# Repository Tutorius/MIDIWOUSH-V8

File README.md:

# MIDIWOUSH-V8
USB-MIDI-CV-Interface with 8 outputs

All Files for the USB-MIDI-CV-Interface with 8 Outputs

a.) Software & Hardware
Files for ARDUINO IDE. Used Hardware ESP32-S3-WROOM (AliExpress), TCA9548A, GY-MCP4728, 1,30"" IIC Display (all AliExpress)
4 push-buttons (AliExpress)

b.) PCB
KiCAD-Files

To Do:

c.) PCB-Production
PCBWay-Link to project

e.) 3D-files
Files for frontplate, mounting-things, casing for use out of modular System

More Info about use and problems:

At the time i did not find a way to alter the "Midi-Name" (Its something like "ESP32S3_DEV MIDI 1"). Would be nice if it can be named "MIDIWOUSH-V8". Will try to get a solution for this.

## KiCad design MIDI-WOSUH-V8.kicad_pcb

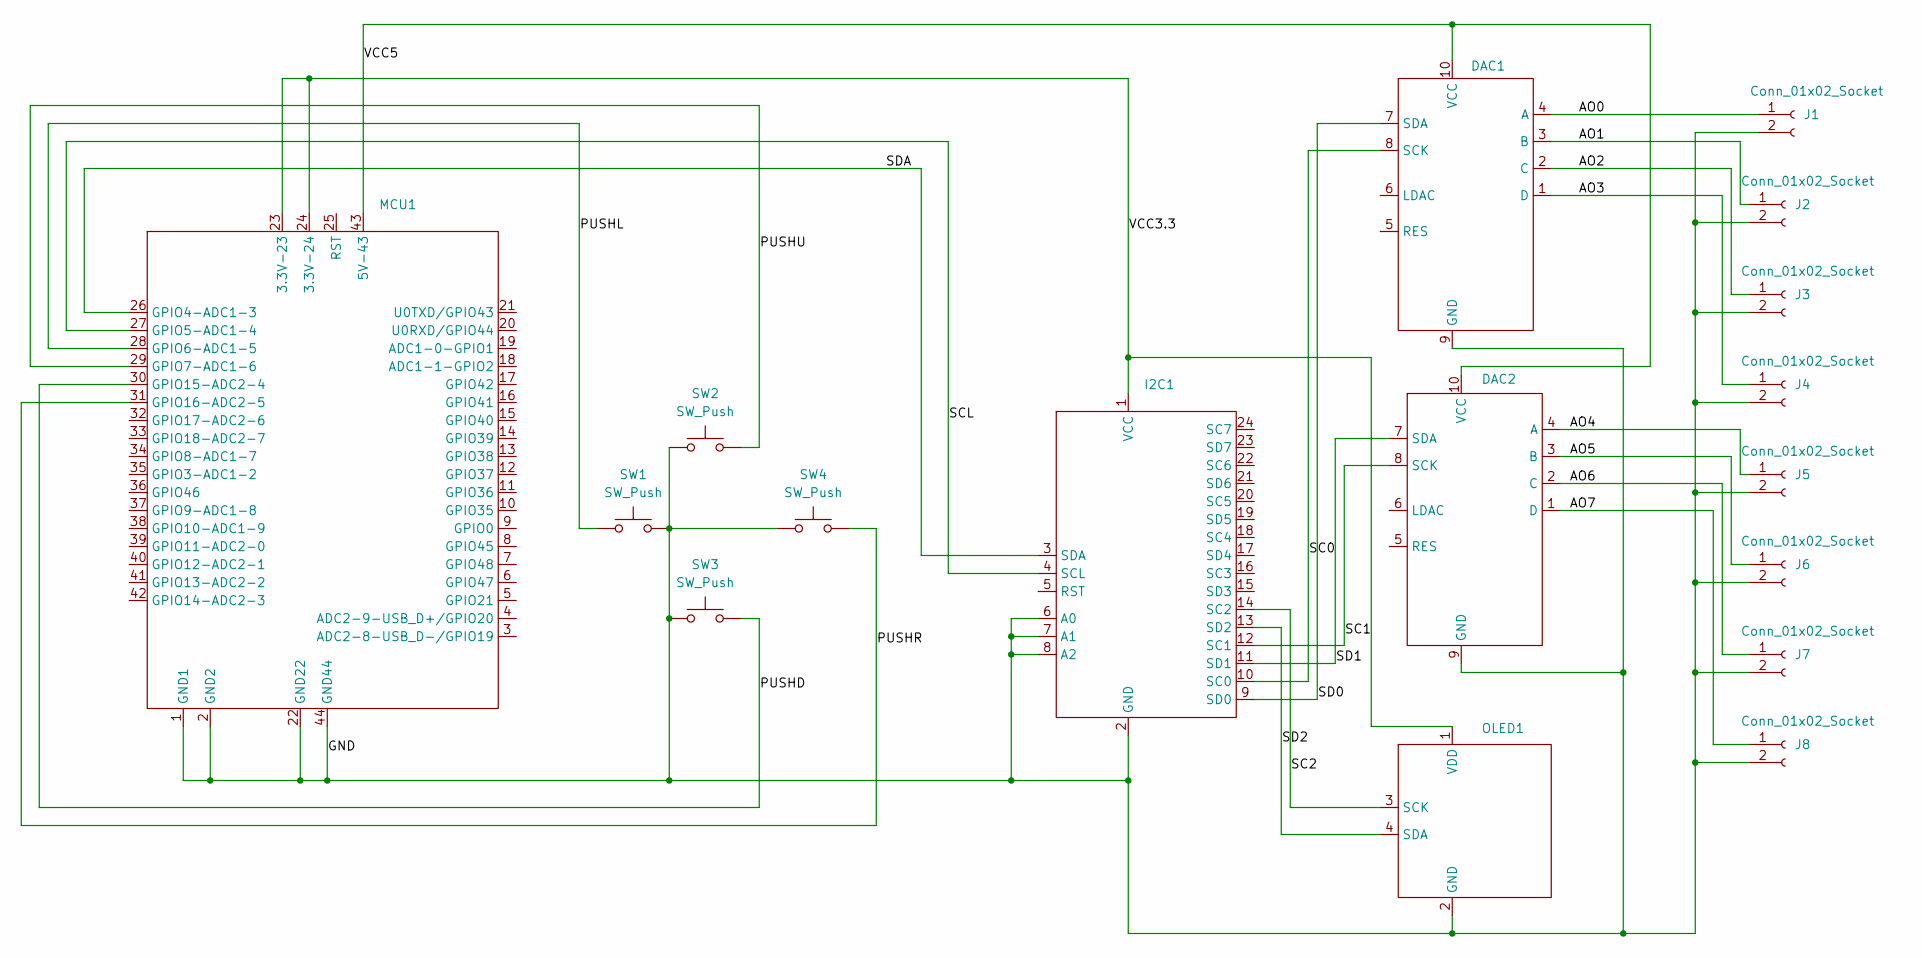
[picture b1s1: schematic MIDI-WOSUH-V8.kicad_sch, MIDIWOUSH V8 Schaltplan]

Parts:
DAC1, DAC2: MCP4728
I2C1: TCA9548A
J1, J2, J3, J4, J5, J6, J7, J8: Conn_01x02_Socket; PinSocket_1x02_P2.54mm_Vertical
MCU1: ESP32-S3-DevKitC-1
OLED1: OLED
SW1, SW2, SW3, SW4: SW_Push; SWITCH1

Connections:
/AO0: DAC1.4 (A), J1.1
/AO1: DAC1.3 (B), J2.1
/AO2: DAC1.2 (C), J3.1
/AO3: DAC1.1 (D), J4.1
/AO4: DAC2.4 (A), J5.1
/AO5: DAC2.3 (B), J6.1
/AO6: DAC2.2 (C), J7.1
/AO7: DAC2.1 (D), J8.1
/GND: DAC1.9 (GND), DAC2.9 (GND), I2C1.2 (GND), I2C1.6 (A0), I2C1.7 (A1), I2C1.8 (A2), J1.2, J2.2, J3.2, J4.2, J5.2, J6.2, J7.2, J8.2, MCU1.1 (GND1), MCU1.2 (GND2), MCU1.22 (GND22), MCU1.44 (GND44), OLED1.2 (GND), SW1.2, SW2.1, SW3.1, SW4.1
/PUSHD: MCU1.30 (GPIO15-ADC2-4), SW3.2
/PUSHL: MCU1.28 (GPIO6-ADC1-5), SW1.1
/PUSHR: MCU1.31 (GPIO16-ADC2-5), SW4.2
/PUSHU: MCU1.29 (GPIO7-ADC1-6), SW2.2
/SC0: DAC1.8 (SCK), I2C1.10 (SC0)
/SC1: DAC2.8 (SCK), I2C1.12 (SC1)
/SC2: I2C1.14 (SC2), OLED1.3 (SCK)
/SCL: I2C1.4 (SCL), MCU1.27 (GPIO5-ADC1-4)
/SD0: DAC1.7 (SDA), I2C1.9 (SD0)
/SD1: DAC2.7 (SDA), I2C1.11 (SD1)
/SD2: I2C1.13 (SD2), OLED1.4 (SDA)
/SDA: I2C1.3 (SDA), MCU1.26 (GPIO4-ADC1-3)
/VCC3.3: I2C1.1 (VCC), MCU1.23 (3.3V-23), MCU1.24 (3.3V-24), OLED1.1 (VDD)
/VCC5: DAC1.10 (VCC), DAC2.10 (VCC), MCU1.43 (5V-43)

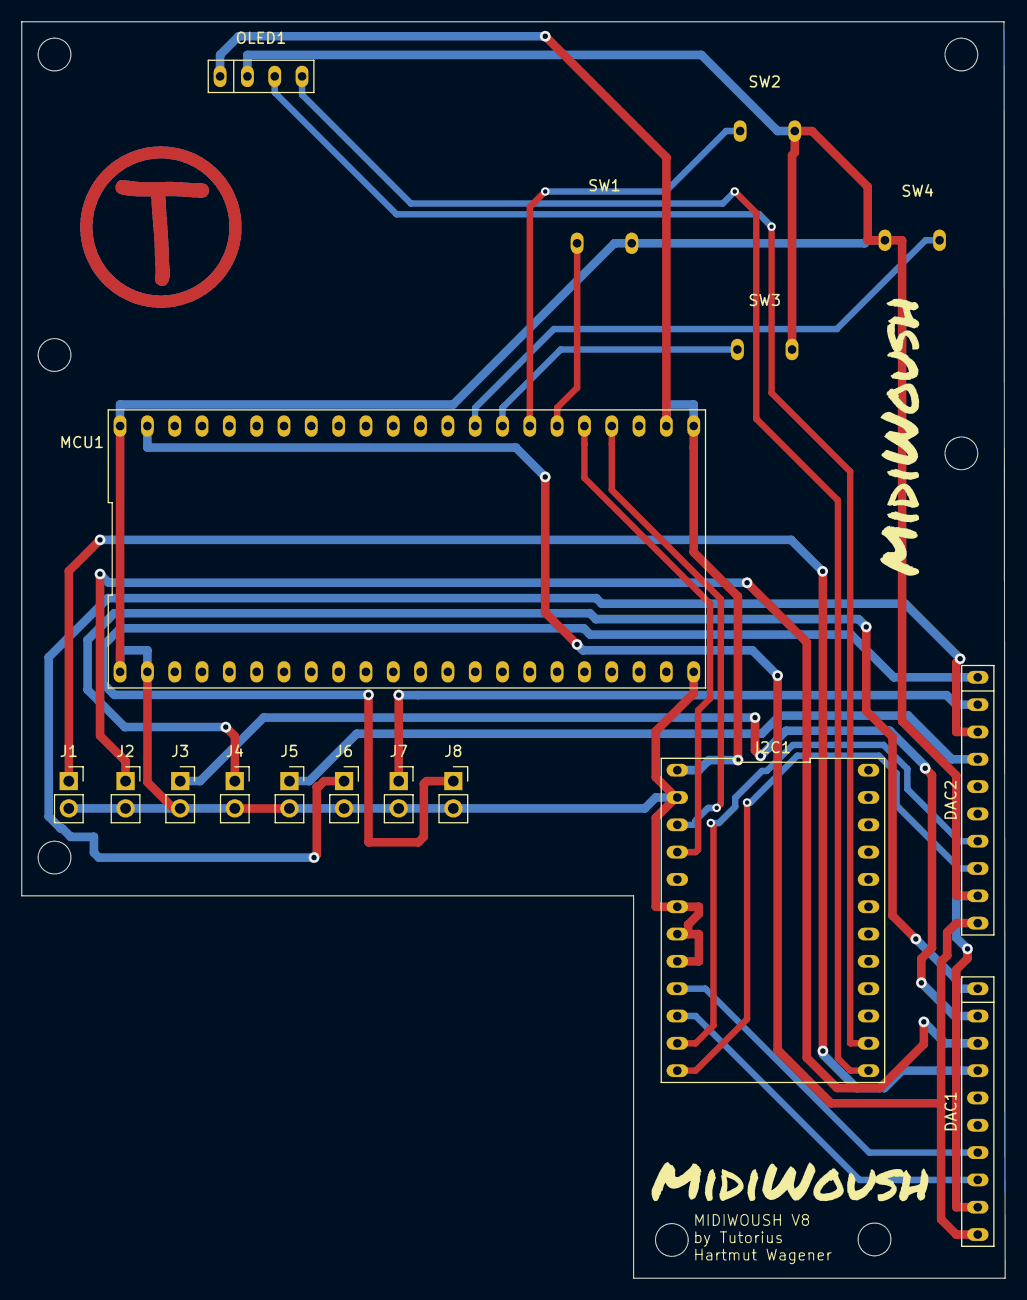
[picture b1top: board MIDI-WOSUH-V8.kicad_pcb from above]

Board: 2 copper layers, 91.4 x 116.8 mm, 17 parts (0 on the bottom side), 23 nets.

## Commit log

2025-07-14 Files for ARDUNO IDE
2025-07-14 KiCAD-Files
2025-07-20 Manual in german and english language
2025-07-20 Update MidiWoush-V8.ino
    New functions, debugging, is final now, i hope... :)
2025-07-20 Settings of Arduino-IDE for uploading to ESP32-S3
    Vital settings for uploading via Arduino-IDE to ESP32-S3-WROOM (preferably on USB-port (left-upper) ) for Tiny-USB-MIDI
2025-08-07 Add files via upload
    Knob for Module (4 times needed)
